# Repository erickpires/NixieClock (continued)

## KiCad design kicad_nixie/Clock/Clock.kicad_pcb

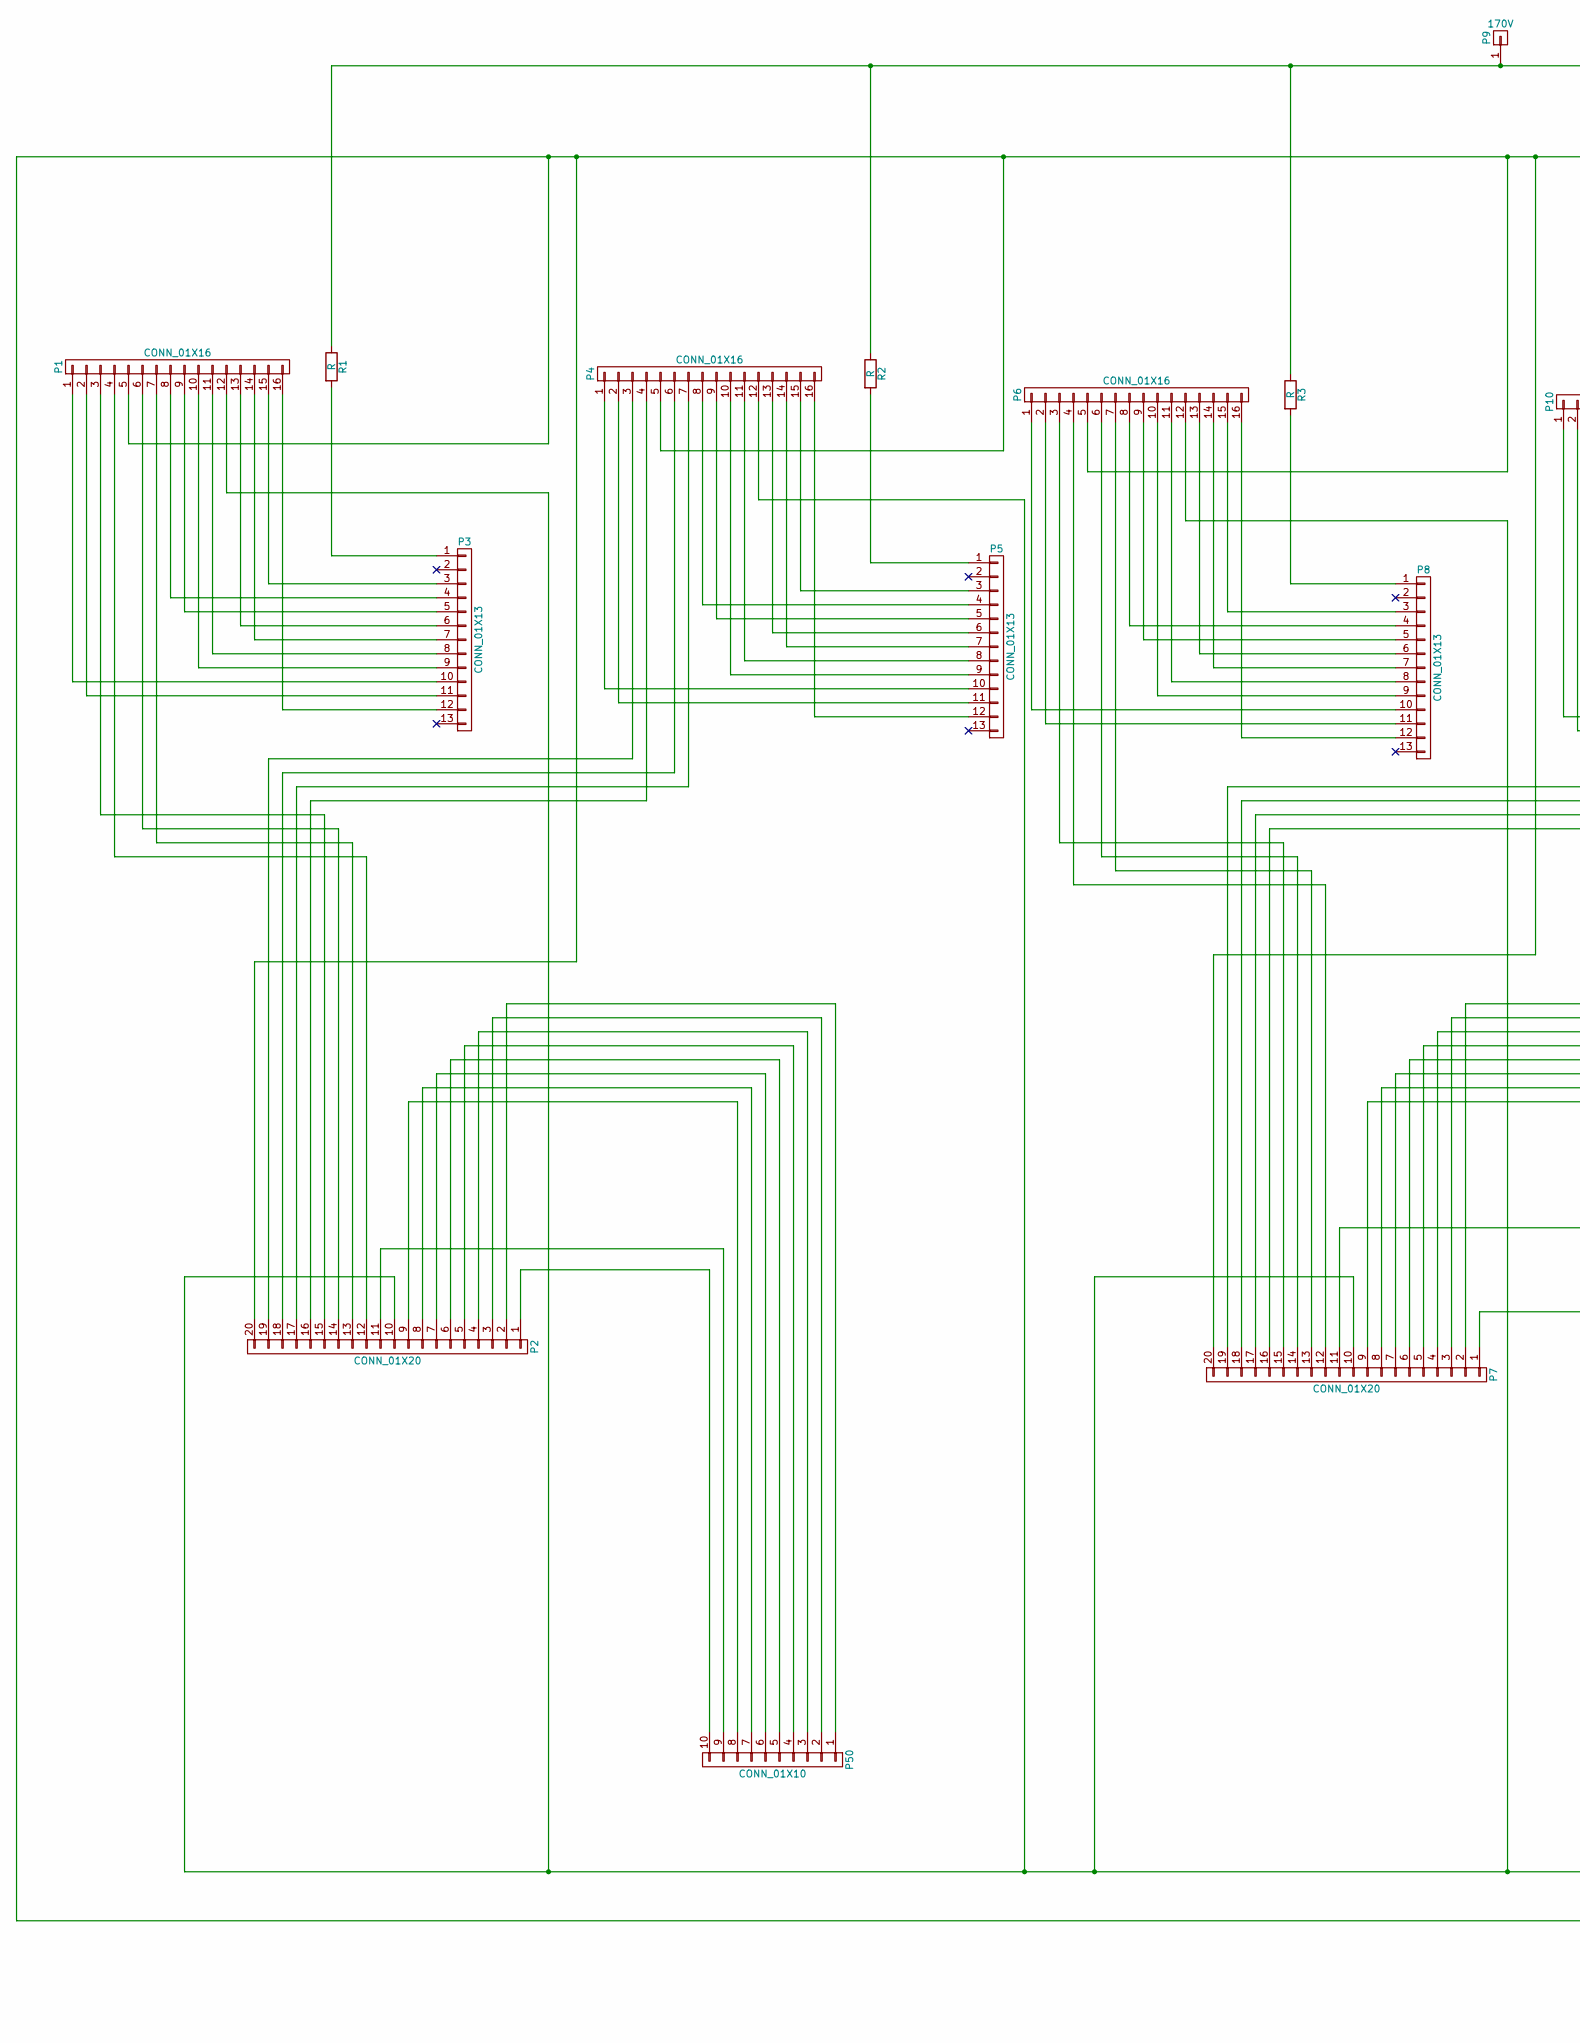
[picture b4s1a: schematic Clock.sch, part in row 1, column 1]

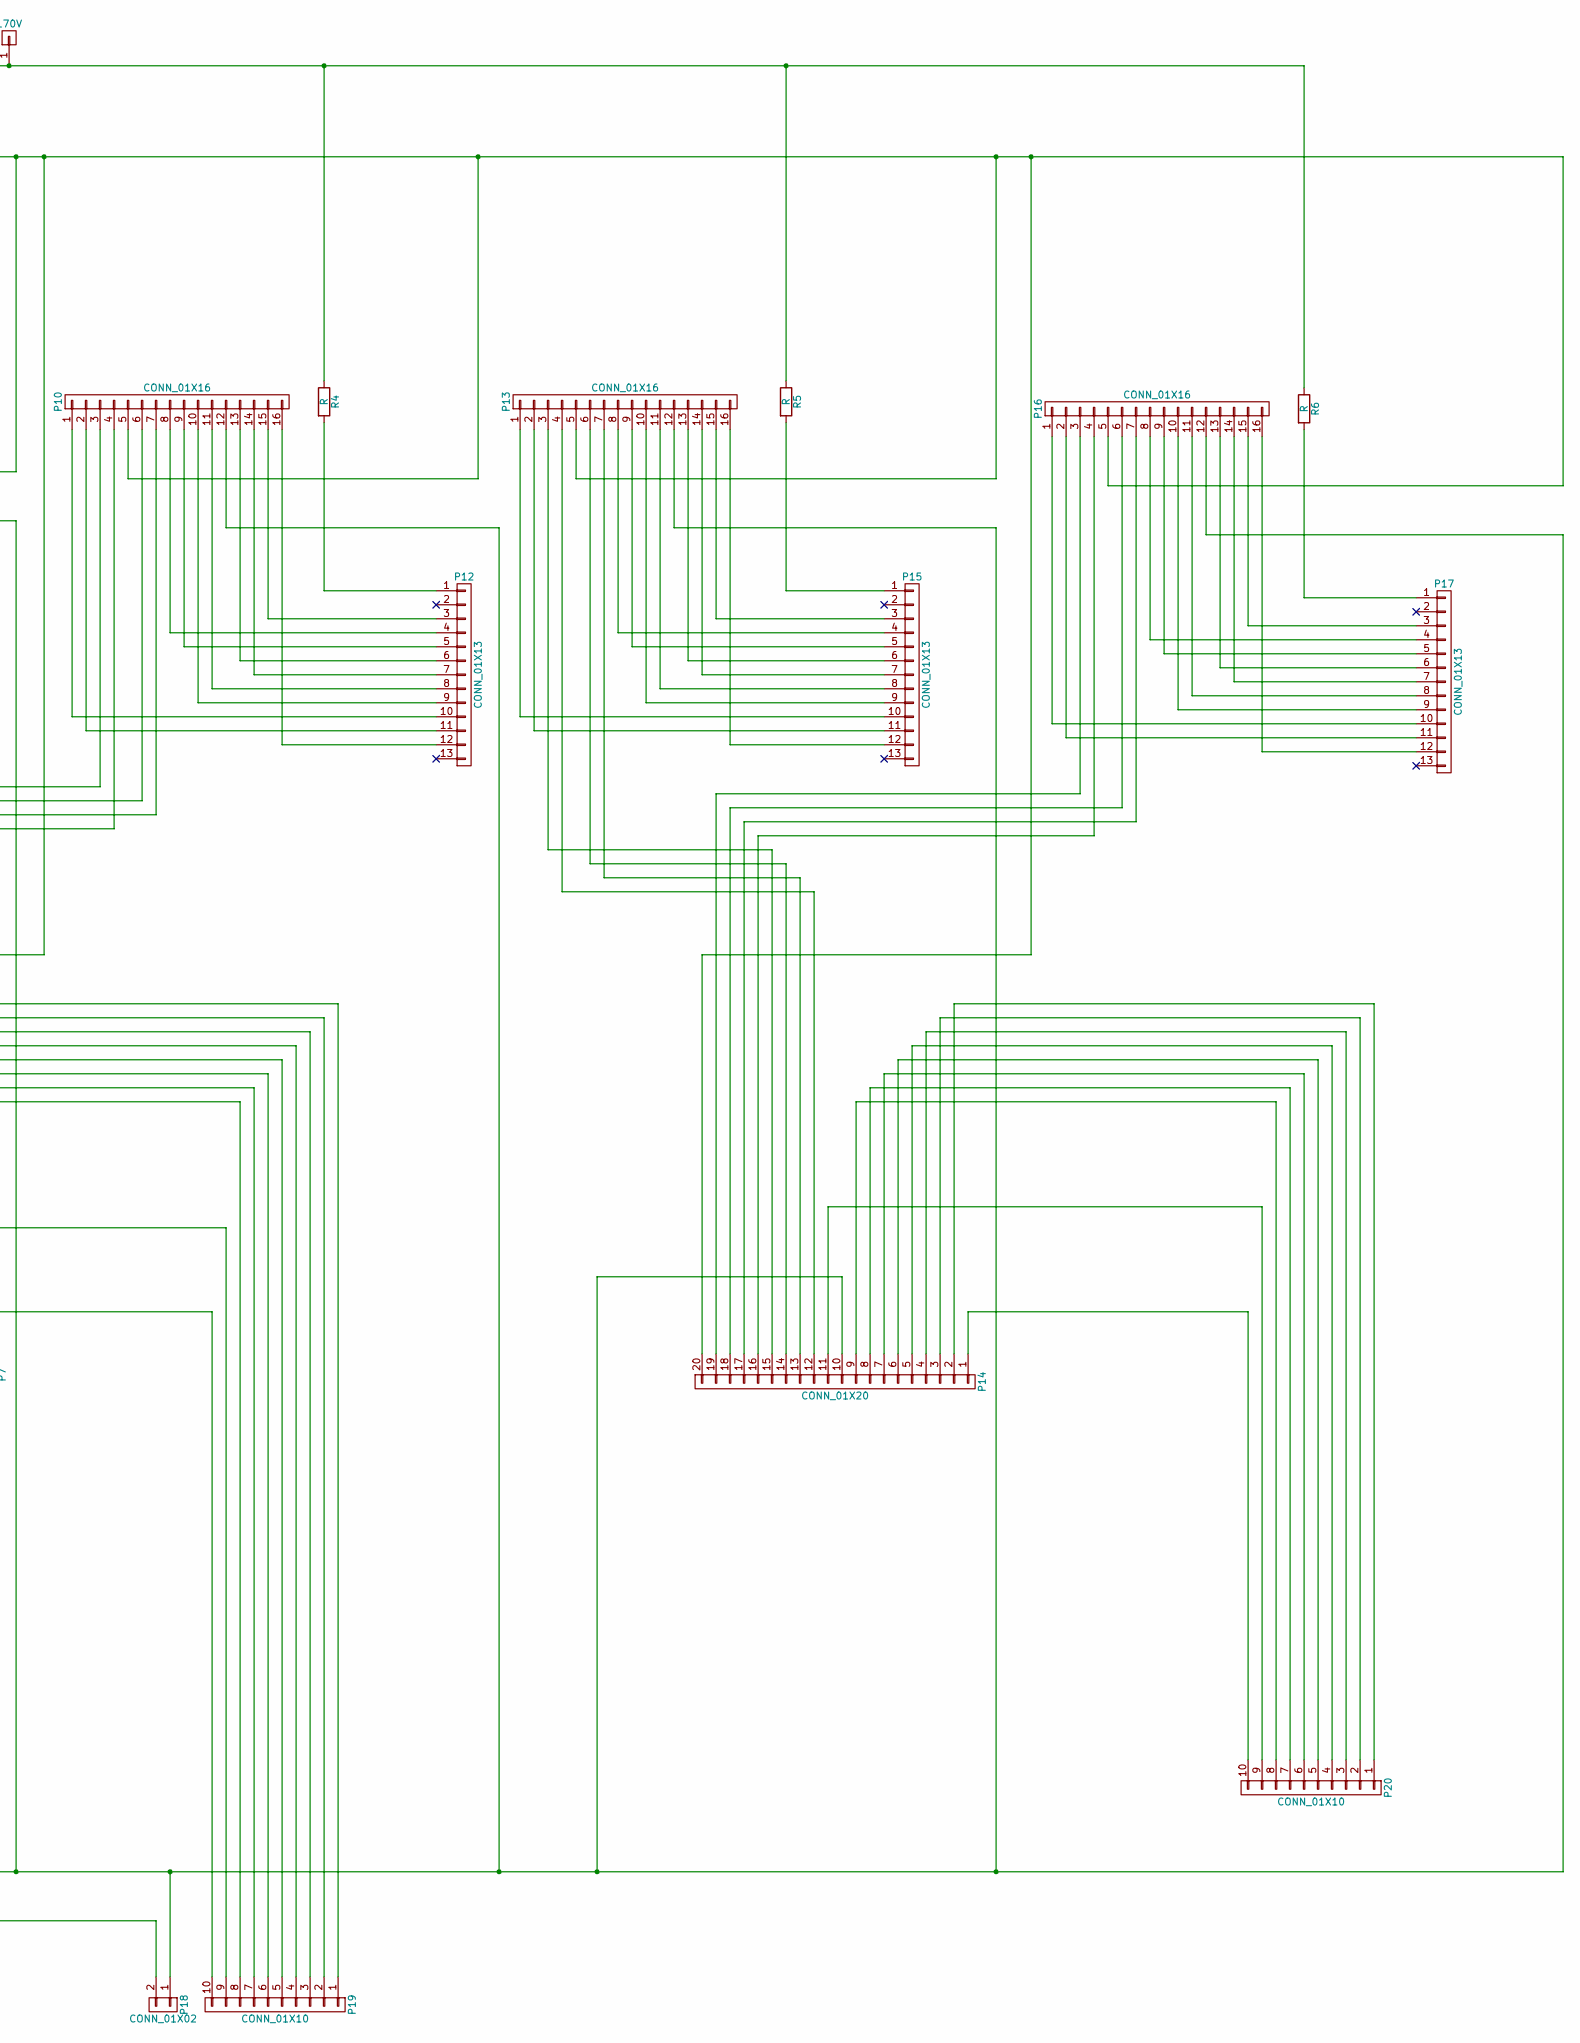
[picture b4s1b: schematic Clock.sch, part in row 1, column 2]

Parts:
P1, P4, P6, P10, P13, P16: CONN_01X16; DIP-16_W7.62mm_LongPads
P2, P7, P14: CONN_01X20; DIP-20_W7.62mm_LongPads
P3, P5, P8, P12, P15, P17: CONN_01X13; IN-14-mod
P9: 170V; Pin_Header_Straight_1x01
P18: CONN_01X02; Pin_Header_Straight_1x02
P19, P20, P50: CONN_01X10; Pin_Header_Straight_1x10
R1, R2, R3, R4, R5, R6: R; Resistor_Horizontal_RM10mm

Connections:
unnamed: P1.1, P3.10
unnamed: P1.2, P3.11
unnamed: P1.3, P2.15
unnamed: P1.4, P2.12
unnamed: P1.5, P2.20, P4.5, P6.5, P7.20, P10.5, P13.5, P14.20, P16.5, P18.2
unnamed: P1.6, P2.14
unnamed: P1.7, P2.13
unnamed: P1.8, P3.4
unnamed: P1.9, P3.5
unnamed: P1.10, P3.9
unnamed: P1.11, P3.8
unnamed: P1.12, P2.10, P4.12, P6.12, P7.10, P10.12, P13.12, P14.10, P16.12, P18.1
unnamed: P1.13, P3.6
unnamed: P1.14, P3.7
unnamed: P1.15, P3.3
unnamed: P1.16, P3.12
unnamed: P2.1, P50.10
unnamed: P2.2, P50.1
unnamed: P2.3, P50.2
unnamed: P2.4, P50.3
unnamed: P2.5, P50.4
unnamed: P2.6, P50.5
unnamed: P2.7, P50.6
unnamed: P2.8, P50.7
unnamed: P2.9, P50.8
unnamed: P2.11, P50.9
unnamed: P2.16, P4.4
unnamed: P2.17, P4.7
unnamed: P2.18, P4.6
unnamed: P2.19, P4.3
unnamed: P3.1, R1.2
unnamed: P4.1, P5.10
unnamed: P4.2, P5.11
unnamed: P4.8, P5.4
unnamed: P4.9, P5.5
unnamed: P4.10, P5.9
unnamed: P4.11, P5.8
unnamed: P4.13, P5.6
unnamed: P4.14, P5.7
unnamed: P4.15, P5.3
unnamed: P4.16, P5.12
unnamed: P5.1, R2.2
unnamed: P6.1, P8.10
unnamed: P6.2, P8.11
unnamed: P6.3, P7.15
unnamed: P6.4, P7.12
unnamed: P6.6, P7.14
unnamed: P6.7, P7.13
unnamed: P6.8, P8.4
unnamed: P6.9, P8.5
unnamed: P6.10, P8.9
unnamed: P6.11, P8.8
unnamed: P6.13, P8.6
unnamed: P6.14, P8.7
unnamed: P6.15, P8.3
unnamed: P6.16, P8.12
unnamed: P8.1, R3.2
unnamed: P9.1, R1.1, R2.1, R3.1, R4.1, R5.1, R6.1
unnamed: P10.1, P12.10
unnamed: P10.2, P12.11
unnamed: P7.19, P10.3
unnamed: P7.16, P10.4
unnamed: P7.18, P10.6
unnamed: P7.17, P10.7
unnamed: P10.8, P12.4
unnamed: P10.9, P12.5
unnamed: P10.10, P12.9
unnamed: P10.11, P12.8
unnamed: P10.13, P12.6
unnamed: P10.14, P12.7
unnamed: P10.15, P12.3
unnamed: P10.16, P12.12
unnamed: P12.1, R4.2
unnamed: P13.1, P15.10
unnamed: P13.2, P15.11
unnamed: P13.3, P14.15
unnamed: P13.4, P14.12
unnamed: P13.6, P14.14
unnamed: P13.7, P14.13
unnamed: P13.8, P15.4
unnamed: P13.9, P15.5
unnamed: P13.10, P15.9
unnamed: P13.11, P15.8
unnamed: P13.13, P15.6
unnamed: P13.14, P15.7
unnamed: P13.15, P15.3
unnamed: P13.16, P15.12
unnamed: P14.1, P20.10
unnamed: P14.2, P20.1
unnamed: P14.3, P20.2
unnamed: P14.4, P20.3
unnamed: P14.5, P20.4
unnamed: P14.6, P20.5
unnamed: P14.7, P20.6
unnamed: P14.8, P20.7
unnamed: P14.9, P20.8
unnamed: P14.11, P20.9
unnamed: P14.16, P16.4
unnamed: P14.17, P16.7
unnamed: P14.18, P16.6
unnamed: P14.19, P16.3
unnamed: P15.1, R5.2
unnamed: P16.1, P17.10
unnamed: P16.2, P17.11
unnamed: P16.8, P17.4
unnamed: P16.9, P17.5
unnamed: P16.10, P17.9
unnamed: P16.11, P17.8
unnamed: P16.13, P17.6
unnamed: P16.14, P17.7
unnamed: P16.15, P17.3
unnamed: P16.16, P17.12
unnamed: P17.1, R6.2
unnamed: P7.2, P19.1
unnamed: P7.3, P19.2
unnamed: P7.4, P19.3
unnamed: P7.5, P19.4
unnamed: P7.6, P19.5
unnamed: P7.7, P19.6
unnamed: P7.8, P19.7
unnamed: P7.9, P19.8
unnamed: P7.11, P19.9
unnamed: P7.1, P19.10

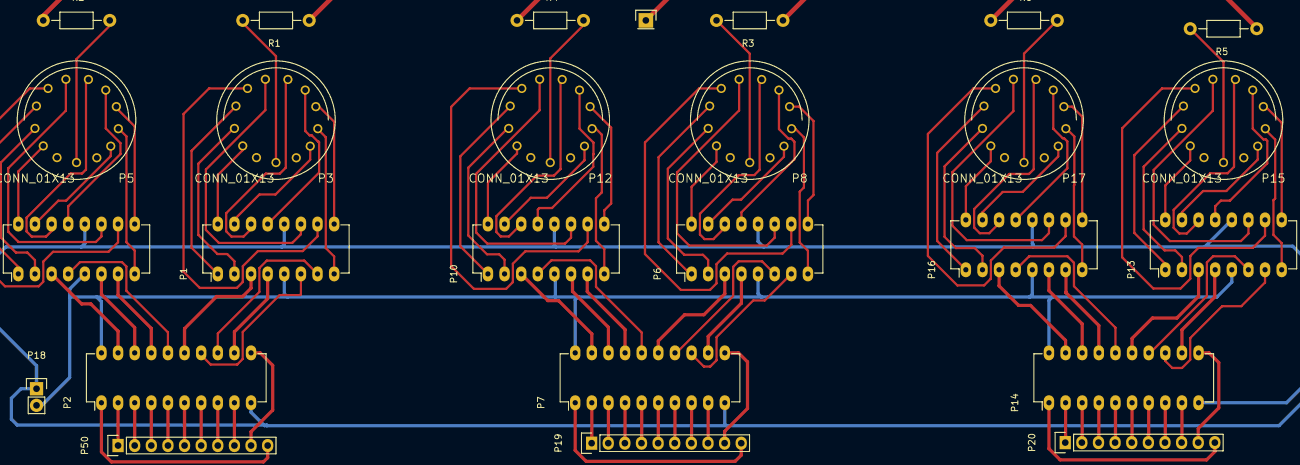
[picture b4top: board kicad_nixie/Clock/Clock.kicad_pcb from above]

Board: 2 copper layers, 26 parts (0 on the bottom side), 123 nets.

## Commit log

2018-05-26 Turn off the display at night
2018-05-26 Added kicad boards files.
2018-05-26 added MIT License.
2018-05-26 Power Supply info.
2018-05-26 Added README.
2018-05-26 Fix README
2018-05-26 Fixed some typos.
2018-05-28 Small correction.
